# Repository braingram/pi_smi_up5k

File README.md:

After reading a post on [iosoft.blog](https://iosoft.blog/) about the
[Raspberry Pi SMI interface](https://iosoft.blog/2020/07/16/raspberry-pi-smi/)
I wanted to test out using the interface for exchanging data with a FPGA.

This project involves some hardware and software (in verilog and python)
designed to test out the interface. There is no specific application for the
project (although I'm open to suggestions).

# Hardware

As described on the [iosoft blog post](https://iosoft.blog/2020/07/16/raspberry-pi-smi/)
SMI can use almost all the Pi GPIO pins. The only non-SMI pins are BCM pins 26 and 27.
A [FPGA hat](lattice_fpga_dev_board) was designed that connects to:

- all SMI pins
- BCM pin 27 as CRESET: to reset the FPGA
- BCM pin 26 as CDONE: to signify the FPGA programming is done
- 5V and GND for power

See [pinouts.csv](docs/pinouts.csv) for a full pinout table. Depending on what
Pi gpio pins your FPGA design uses you may have to disable several Pi interfaces
by modifying /boot/config.txt, removing kernel modules, and/or directly changing
gpio modes.

:exclamation: WARNING :exclamation: It is possible to have the Pi and FPGA fight
to drive pins which can cause regulators to get hot and magic blue smoke to escape.

The hat uses a lattice ice40-up5k in a 48-pin QFN package. The remaining FPGA pins
connect to:

- RGB led (using up5k led drivers)
- a 2x6 PMOD connector (:exclamation: WARNING :exclamation: the power and ground are swapped on the current design)

The hat does not include an oscillator and instead the up5k internal oscillator should be used.

## FPGA bitstream

For generating bitstreams the open source [icestorm](http://www.clifford.at/icestorm/) and [nextpnr](https://github.com/YosysHQ/nextpnr) tools were used.
The hat also does not include spi flash to hold the FPGA bitstream and the SPI_SS
pin of the FPGA is pulled low with a 10K resistor. To load a bitstream onto the
FPGA the Pi pins must be setup for SPI and the bistream sent to the FPGA using
a [custom python script](program.py) (similar to iceprog).

```bash
# enable SPI
sudo dtparam spi=on
# run in the same directory as program.py and provide a path to your bitstream file
python3 program.py bitstream.bit
```

# Software

The software for the project includes verilog and python code. The python
[program.py](program.py) script is used to reset and program the FPGA over
SPI. Other python scripts are included in some example project directories:

- [blink](blink): blink FPGA RGB leds
- [testpins](testpins): test (almost) all FPGA/Pi connections
- [spi](spi): FPGA as spi peripheral
- [spram](spram): read FPGA SPRAM over spi
- [smi](smi): read incrementing counter on FPGA over smi

Each example project includes verilog code, a Makefile for building the bitstream and
some contain python scripts for testing/interacting with the programmed FPGA.

# SMI Notes

## Using the SMI character device linux kernel modules

All of the testing used the [bcm2835_smi](https://github.com/raspberrypi/linux/blob/rpi-5.4.y/include/linux/broadcom/bcm2835_smi.h) and smi-dev kernel modules.
To load the modules several Pi peripherals must be disabled (i2c, spi, uart, etc).
When correctly loaded a character device should appear at /dev/smi
This character device can be read from to initiate reads on the SMI bus and
written to to initiate writes on the SMI bus. Settings can be changed by
issuing ioctl system calls.
Setting descriptions can be found in [bcm2835_smi.h](https://github.com/raspberrypi/linux/blob/rpi-5.4.y/include/linux/broadcom/bcm2835_smi.h#L68).
Defaults for these settings can be found in [bcm2835_smi.c](https://github.com/raspberrypi/linux/blob/rpi-5.4.y/drivers/misc/bcm2835_smi.c#L128).
The ioctl magic number is [0x1](https://github.com/raspberrypi/linux/blob/rpi-5.4.y/include/linux/broadcom/bcm2835_smi.h#L48)
and 3 types of requests are accepted:

- 0x0100: get settings
- 0x0101: set settings
- 0x0102: address

Get/set settings expect a Settings struct/Structure (as described in [bcm2835_smi.h](https://github.com/raspberrypi/linux/blob/rpi-5.4.y/include/linux/broadcom/bcm2835_smi.h#L68))
Address accepts an (up to 6 bit) address that will be asserted on the SMI bus
during read/write cycles.

## Pin electrical specs

### Address pins

SA5:SA0 are normally high (3.3 volts) and are asserted just prior to and
slightly after a read/write cycle (see the smi settings setup, hole, pace,
and strobe settings). SA5 is the most significant bit and a 0 address bit
results in a low (0 volt) signal. With the default settings the address
bus asserts ~8 ns prior to the read/write signal (see below) and deasserts
~8 ns after the read/write signal inactivates.

It seems like the smi driver is OK with not commanding all address pins
which could open up a few signals on the Pi.

### Control pins [SOE/SE, SWE/SRW]

SOE/SE is normally high and goes low during a read cycle

SWE/SRW is normally high and goes low during a write cycle

For both signals and default settings the low period is ~24 ns.

### Data pins

:exclamation: So far only pins SD0 to SD15 have been tested

These pins appear to be driven low when not in a read/write cycle which
means the FPGA must release (put into high-z) these pins when not
in a read cycle.

I'm not sure at what edge of SOE/SE the Pi reads the data pins but based
off NAND datasheets and iosoft notes I think it's the rising edge of SOE/SE.
This gives the FPGA ~24 ns from falling edge and ~32 ns from address
assertion to assert the data lines.

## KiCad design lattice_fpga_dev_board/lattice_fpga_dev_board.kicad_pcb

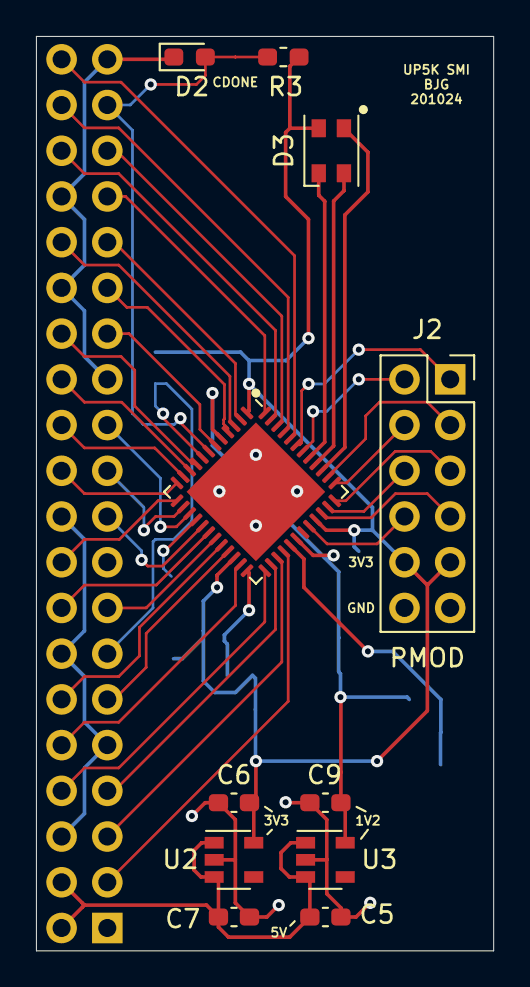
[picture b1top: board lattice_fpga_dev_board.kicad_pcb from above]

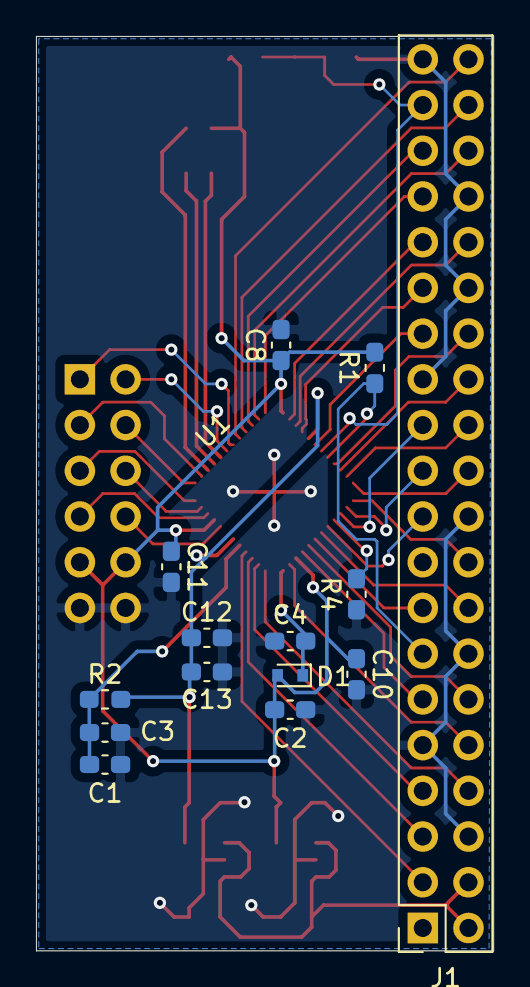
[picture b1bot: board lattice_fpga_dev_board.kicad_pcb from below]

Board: 2 copper layers, 25.4 x 50.8 mm, 25 parts (14 on the bottom side), 46 nets.

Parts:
C1, C2, C12: 0.1u; C_0603_1608Metric_Pad1.08x0.95mm_HandSolder
C3, C4, C5, C6, C7, C8, C9, C10, C11, C13: 4.7u; C_0603_1608Metric_Pad1.08x0.95mm_HandSolder
D1: 1N4148WT-7; D_SOD-523
D2: LED; LED_0603_1608Metric_Pad1.05x0.95mm_HandSolder
D3: LED_BGRA; LED_Cree-PLCC4_3.2x2.8mm_CCW
J1: Raspberry_Pi_2_3; PinSocket_2x20_P2.54mm_Vertical
J2: PMOD; PinSocket_2x06_P2.54mm_Vertical
R1: 10K; R_0603_1608Metric_Pad1.05x0.95mm_HandSolder
R2: 100; R_0603_1608Metric_Pad1.05x0.95mm_HandSolder
R3: 2.2K; R_0603_1608Metric_Pad1.05x0.95mm_HandSolder
R4: 10K; C_0603_1608Metric_Pad1.08x0.95mm_HandSolder
U1: ICE40UP5K-SG48ITR; QFN-48-1EP_7x7mm_P0.5mm_EP5.45x5.45mm
U2: AP2127K-3.3; SOT-23-5
U3: AP2127K-1.2; SOT-23-5

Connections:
+1V2: C9.1, C12.1, C13.1, R2.2, U1.5, U1.30, U3.5
+2V5: C4.1, D1.1, U1.24
+3V3: C2.1, C6.1, C8.1, C10.1, C11.1, D1.2, D3.4, J2.9, J2.10, R1.2, R3.2, U1.1, U1.22, U1.33, U2.5
+5V: C5.1, C7.1, J1.2, J1.4, U2.1, U2.3, U3.1, U3.3
/CDONE: D2.2, J1.37, R3.1, U1.7
/CRESET: J1.13, R1.1, U1.8
/LED_B: D3.1, U1.41
/LED_G: D3.2, U1.40
/LED_R: D3.3, U1.39
/PMOD1: J2.2, U1.42
/PMOD2: J2.4, U1.37
/PMOD3: J2.6, U1.35
/PMOD4: J2.8, U1.32
/PMOD7: J2.1, U1.43
/PMOD8: J2.3, U1.38
/PMOD9: J2.5, U1.36
/PMOD10: J2.7, U1.34
/SA0: J1.29, U1.4
/SA1: J1.7, U1.26
/SA2: J1.5, U1.27
/SA3: J1.3, U1.28
/SA4: J1.28, U1.9
/SA5: J1.27, U1.6
/SD0: J1.24, U1.11
/SD1_MISO: J1.21, U1.14
/SD2_MOSI: J1.19, U1.17
/SD3_SCLK: J1.23, U1.15
/SD4: J1.32, U1.3
/SD5: J1.33, U1.48
/SD6: J1.8, U1.25
/SD7: J1.10, U1.23
/SD8: J1.36, U1.47
/SD9: J1.11, U1.21
/SD10: J1.12, U1.20
/SD11: J1.35, U1.46
/SD12: J1.38, U1.45
/SD13: J1.40, U1.44
/SD14: J1.15, U1.19
/SD15: J1.16, U1.18
/SD16: J1.18, U1.13
/SD17: J1.22, U1.12
/SOE_SE: J1.31, U1.2
/SPI_SS: R4.2, U1.16
/SWE_SRW: J1.26, U1.10
/VCC_PLL: C1.1, C3.1, R2.1, U1.29
GND: C1.2, C2.2, C3.2, C4.2, C5.2, C6.2, C7.2, C8.2, C9.2, C10.2, C11.2, C12.2, C13.2, D2.1, J1.6, J1.9, J1.14, J1.20, J1.25, J1.30, J1.34, J1.39, J2.11, J2.12, R4.1, U1.49, U2.2, U3.2

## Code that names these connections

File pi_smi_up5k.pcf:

# spi pins (overlaps with gpio/smi) [pi names]
set_io SPI_CE0 10
set_io SPI_CE1 11
set_io SPI_MISO 14
set_io SPI_MOSI 17
set_io SPI_SCLK 15

# i2c pins (overlaps with gpio/smi) no HW pullups [pi names]
set_io I2C_SDA0 6
set_io I2C_SCL0 9
set_io I2C_SDA1 28
set_io I2C_SCL1 27

# uart pins (overlaps with gpio/smi) [pi names]
set_io UART_TX 25
set_io UART_RX 23

# pcm pins (overlaps with gpio/smi) [pi names]
set_io PCM_CLK 20
set_io PCM_FS 46
set_io PCM_DIN 45
set_io PCM_DOUT 44

# pwm pins (overlaps with gpio/smi) [pi names]
set_io PWM0 3
set_io PWM1 48

# gpclk pins (overlaps with gpio/smi) [pi names]
set_io GPCLK0 26
set_io GPCLK1 4
set_io GPCLK2 2

# blinky blinky
set_io RGB0 39  # blue
set_io RGB1 40  # green
set_io RGB2 41  # red

# GPI pins (takes ALL pi pins)
set_io GPIO0 6
set_io GPIO1 9
set_io GPIO2 28
set_io GPIO3 27
set_io GPIO4 26
set_io GPIO5 4
set_io GPIO6 2
set_io GPIO7 10
set_io GPIO8 11
set_io GPIO9 14
set_io GPIO10 17
set_io GPIO11 15
set_io GPIO12 3
set_io GPIO13 48
set_io GPIO14 25
set_io GPIO15 23
set_io GPIO16 47
set_io GPIO17 21
set_io GPIO18 20
set_io GPIO19 46
set_io GPIO20 45
set_io GPIO21 44
set_io GPIO22 19
set_io GPIO23 18
set_io GPIO24 13
set_io GPIO25 12

# SMI pins (takes ALL pi pins)
set_io SMI_SA5 6
set_io SMI_SA4 9
set_io SMI_SA3 28
set_io SMI_SA2 27
set_io SMI_SA1 26
set_io SMI_SA0 4
set_io SMI_SOE 2
set_io SMI_SWE 10
set_io SMI_SD0 11
set_io SMI_SD1 14
set_io SMI_SD2 17
set_io SMI_SD3 15
set_io SMI_SD4 3
set_io SMI_SD5 48
set_io SMI_SD6 25
set_io SMI_SD7 23
set_io SMI_SD8 47
set_io SMI_SD9 21
set_io SMI_SD10 20
set_io SMI_SD11 46
set_io SMI_SD12 45
set_io SMI_SD13 44
set_io SMI_SD14 19
set_io SMI_SD15 18
set_io SMI_SD16 13
set_io SMI_SD17 12

# pmod pins (no overlap with smi/pi)
set_io PMOD1 42
set_io PMOD2 37
set_io PMOD3 35
set_io PMOD4 32
set_io PMOD7 43
set_io PMOD8 38
set_io PMOD9 36
set_io PMOD10 34

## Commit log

2020-11-04 adding blank readme
2020-11-04 adding simple blink verilog example with python programming script
2020-11-04 adding kicad files
2020-11-05 adding verilog for script to test pins
2020-11-05 adding python script to test gpio-fpga pins
2020-11-09 adding pinout csv file
2020-11-09 starting spi verilog code
2020-11-09 adding reset script and python test spi script
2020-11-09 fixing simple spi test verilog
2020-11-10 minor updates to spi test
2020-11-10 adding spram test
2020-11-11 started smi notes and scripts
2020-11-11 smi settings change, tested 8 bit mode
2020-11-11 simple smi write from fpga, read from pi
2020-11-11 high z smi data pins on address mismatch to avoid overloading 3v3
2020-11-11 updating README
2020-11-11 more README updates
